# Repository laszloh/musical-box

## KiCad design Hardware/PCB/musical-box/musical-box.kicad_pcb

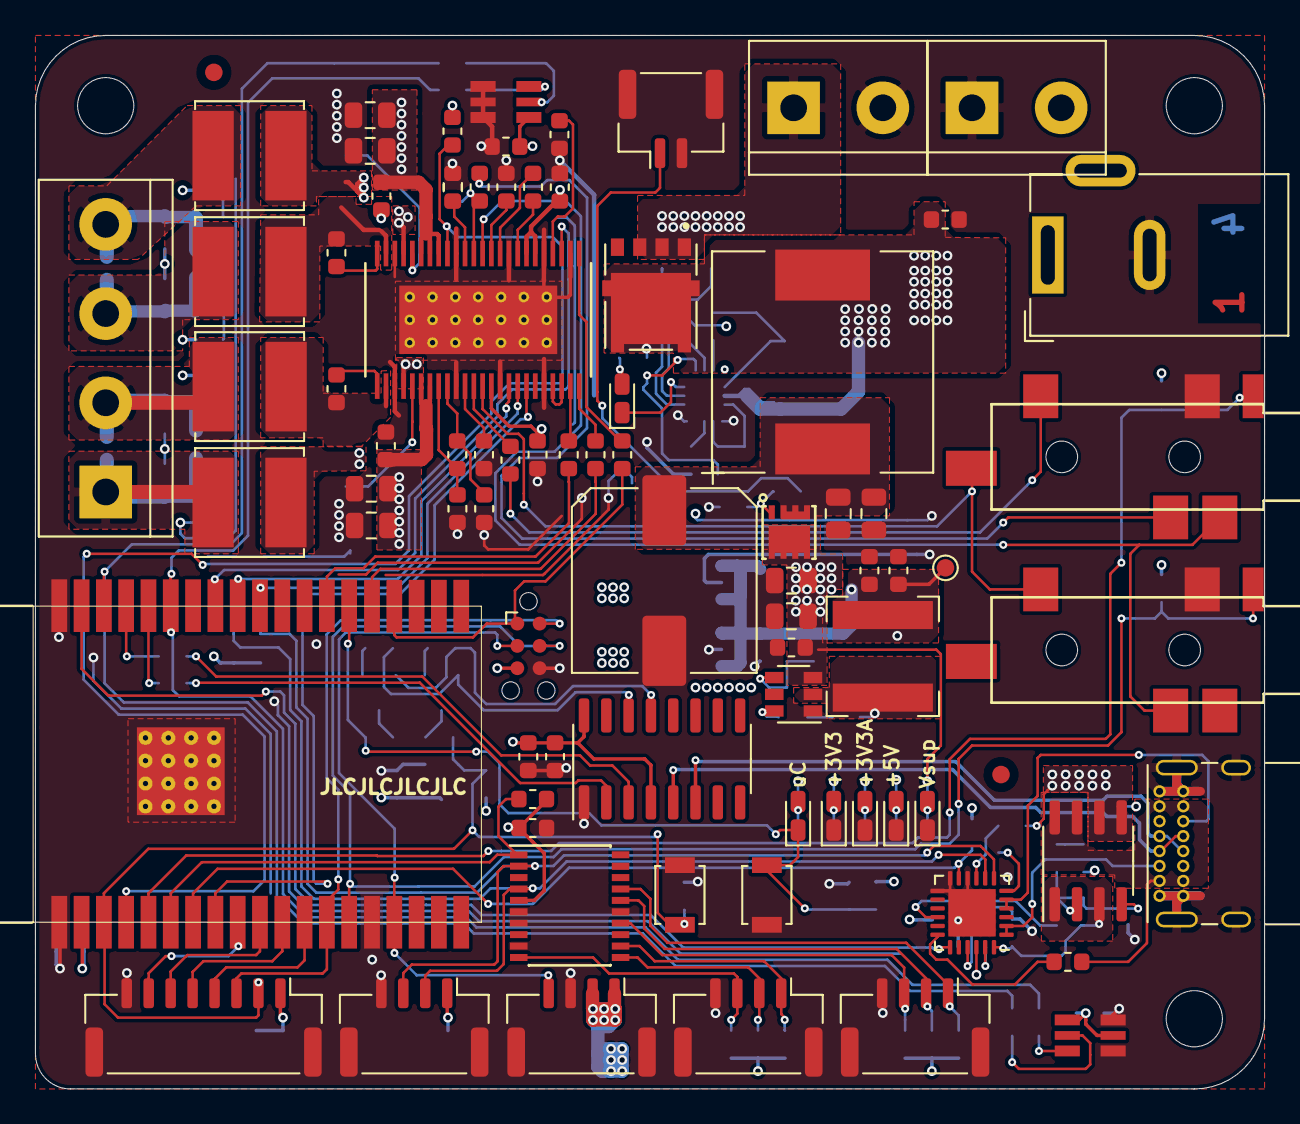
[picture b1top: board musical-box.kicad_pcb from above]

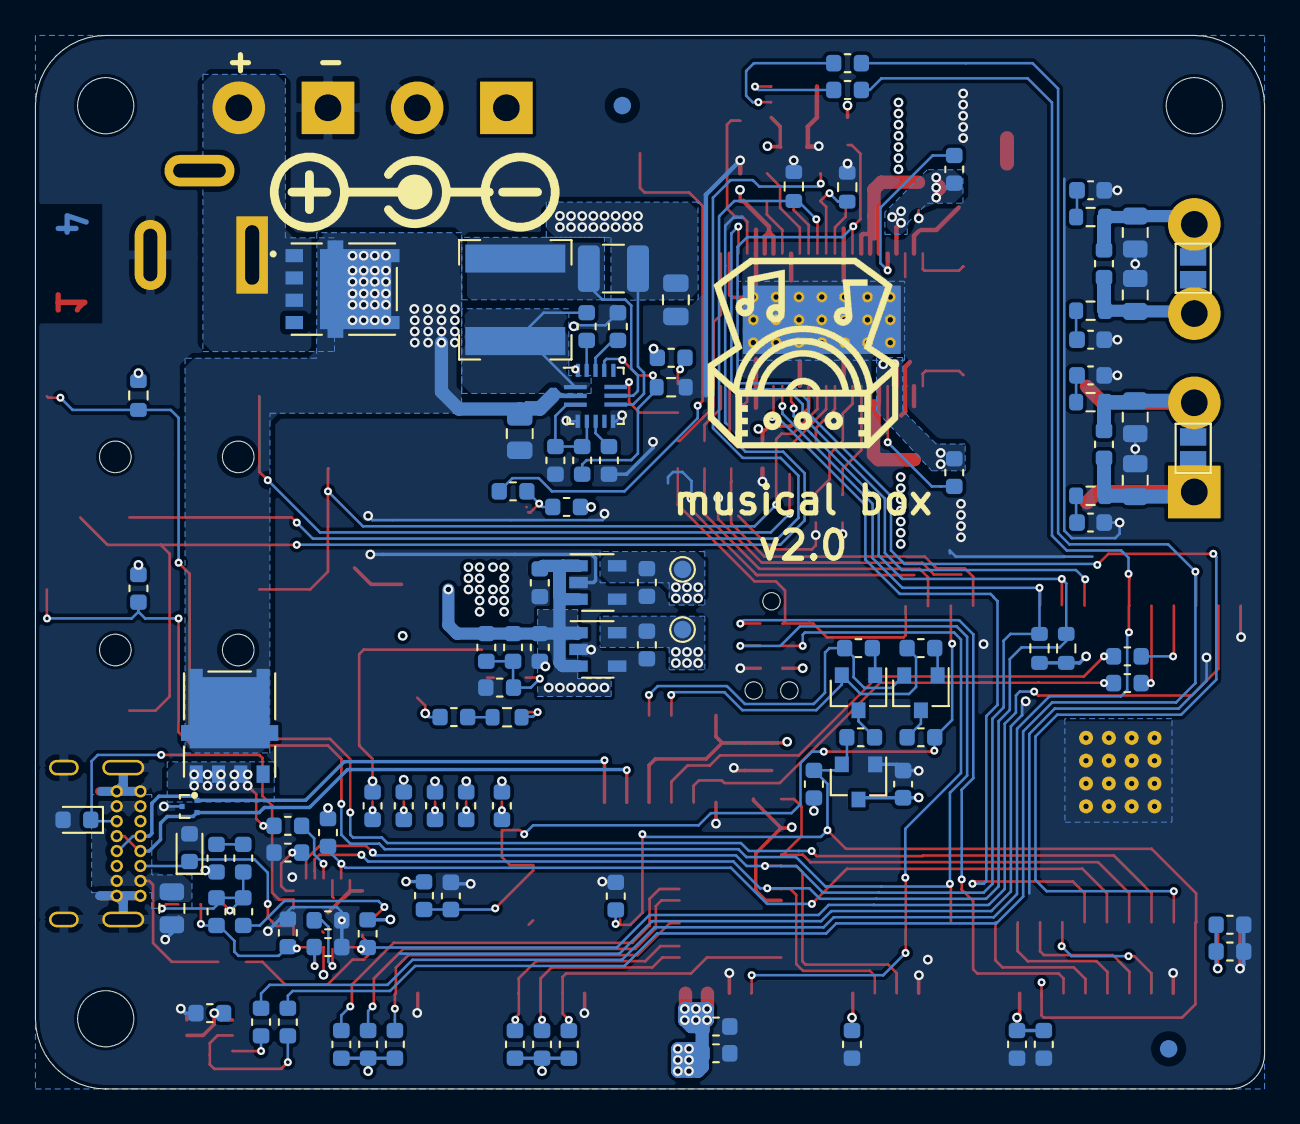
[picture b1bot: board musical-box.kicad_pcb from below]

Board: 4 copper layers, 70.0 x 60.0 mm, 192 parts (107 on the bottom side), 121 nets.

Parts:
C201, C203, C207, C211, C212, C218, C222, C505, C506, C527, C528: 10u; C_0805_2012Metric
C202: 270u; CP_Elec_10x10
C204, C208, C209, C214, C215, C301, C303, C402, C406, C503, C507, C511, C512, C517, C518, C521, C522, C524, C525: 2.2u; C_0603_1608Metric
C205, C206, C213, C216, C223, C224, C225, C227, C302, C304, C305, C306, C401, C403, C404, C405, C501, C502, C504, C508, C513, C515, C520, C526: 100n; C_0603_1608Metric
C217, C220, C221, C226: 22u; C_0603_1608Metric
C219, C510, C519: 100p; C_0603_1608Metric
C509, C514, C516, C523: 680n; C_0805_2012Metric
C529, C530, C531, C532: 10n; C_0603_1608Metric
D102, D203, D205, D207, D208, D209: LED; LED_0603_1608Metric_Castellated
D201, D204, D210: NTS1045EMFST1G; DIO_NTS1045EMFST1G
D202, D206: 24V; D_0603_1608Metric
FID101, FID102, FID103, FID104: Fiducial; Fiducial_1mm_Mask2mm
H101, H102, H104: MountingHole; MountingHole_3.2mm_M3
J1: power; JST_GH_BM02B-GHS-TBT_1x02-1MP_P1.25mm_Vertical
J201: PSU; TerminalBlock_bornier-2_P5.08mm
J202: Jack-DC; BarrelJack_Wuerth_6941xx301002
J203: BATT; TerminalBlock_bornier-2_P5.08mm
J301: JTAG; Tag-Connect_TC2030-IDC-NL_2x03_P1.27mm_Vertical
J401: SPI Display; JST_GH_BM08B-GHS-TBT_1x08-1MP_P1.25mm_Vertical
J402: Rotary Encoder 1; JST_GH_BM04B-GHS-TBT_1x04-1MP_P1.25mm_Vertical
J403: I2C Display; JST_GH_BM04B-GHS-TBT_1x04-1MP_P1.25mm_Vertical
J404: Rotary Encoder 2; JST_GH_BM04B-GHS-TBT_1x04-1MP_P1.25mm_Vertical
J405: WS2812; JST_GH_BM04B-GHS-TBT_1x04-1MP_P1.25mm_Vertical
J501: spk_out; TerminalBlock_bornier-4_P5.08mm
J502: aux in; PJ328B
J503: line out; PJ328B
JP3, JP4: mono; SolderJumper-2_P1.3mm_Open_Pad1.0x1.5mm
L201: 2,2u; L_12x12mm_H8mm
L202, L203: 6.8u; L_Bourns-SRN6028
L501, L502, L503, L504: 4.7u; L_Bourns_SRN6045TA
P201: USB_C; USB_C_Receptacle_GCT_USB4085
P202, P203, P204: ICT-Point; TestPoint_Pad_D1.0mm
Q201: IRFHM9331; PQFN-3x3
Q204: IRF9362; SOIC-8_3.9x4.9mm_P1.27mm
Q301, Q302: BC848; SOT-23
R101, R102, R103, R223, R501, R504, R505, R512: 10R; R_0603_1608Metric
R105, R106, R107, R207, R210, R217, R218, R221, R222, R305, R308, R312, R401, R402, R403, R404, R405, R406: 1k; R_0603_1608Metric
R201, R203, R205, R208, R209, R211, R213, R214, R215, R216, R220, R407, R409, R508, R509, R513: 10k; R_0603_1608Metric
R202, R204: 100k; R_0603_1608Metric
R206, R302, R303, R304, R309: 220R; R_0603_1608Metric
R212: 100mR; R_1210_3225Metric
R219: 52.3k; R_0603_1608Metric
R408, R410: 50m; R_0603_1608Metric
R502: 750k; R_0603_1608Metric
R503: 150k; R_0603_1608Metric
R506, R507, R510, R511: 3.3R; R_0603_1608Metric
SW301: boot; SW_SPST_B3U-1000P
SW302: reset; SW_SPST_B3U-1000P
U201: STUSB4500QTR; QFN-24-1EP_4x4mm_P0.5mm_EP2.7x2.7mm
U202: MP2615; QFN-16_2.9x2.9_Pitch0.5mm
U203: TPS56339; SOT-23-6
U204, U205: TLV75733PDBV; SOT-23-5
U206: TLV803EC30DBZR; SOT-23
U207: TPD2EUSB30A; Texas_DRT-3
U301: CH340C; SOIC-16_3.9x9.9mm_P1.27mm
U302: ESP32-WROVER
U401: PCF8574ATS; SSOP-20_4.4x6.5mm_P0.65mm
U501, U502: SPH0644HM4H-1
U503: TAS5754MDCA

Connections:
+3.3VA: C226.2, C501.1, C502.1, C507.1, P203.1, R221.2, U205.5, U501.1, U501.5, U502.1, U503.14
+3V3: C221.2, C227.2, C301.1, C302.1, C303.1, C304.1, C401.1, C402.1, C403.1, C404.1, C524.1, J301.5, J401.1, J403.1, P202.1, R105.2, R106.2, R107.2, R213.1, R214.1, R217.2, R222.1, R312.2, R401.1, R402.1, R403.1, R404.1, R405.1, R406.1, R407.1, R508.2, R509.2, R513.2, U201.22, U204.5, U206.3, U301.4, U301.16, U302.2, U401.5, U503.30, U503.31
+5V: C217.2, C219.2, C220.2, C223.2, C225.2, C405.1, C406.1, J405.1, J405.2, L203.2, P204.1, R218.2, R219.1, U204.1, U204.3, U205.1, U205.3
+15V: C218.2, C222.2, C224.2, C504.1, C505.1, C506.1, C526.1, C527.1, C528.1, Q201.3, R201.2, U203.3, U503.6, U503.7, U503.41, U503.42, U503.43
/Audio Output/AUX_Detect: J502.S, R513.1, U302.5
/Audio Output/DAC_OUTA: J502.TN, J503.T, U503.13
/Audio Output/DAC_OUTB: J502.R1N, J503.R1, R409.2, U503.36
/Audio Output/GPIO0: U302.8, U503.18
/Audio Output/GPIO2: U503.21, U503.22
/Audio Output/LRCLK: R101.1, U503.25
/Audio Output/OUT1+: C509.1, C510.1, J501.1, JP3.1, L501.2, R506.2
/Audio Output/OUT1-: C510.2, C514.1, J501.2, JP3.2, L502.2, R507.2
/Audio Output/OUT2+: C519.2, C523.1, J501.4, JP4.2, L504.2, R511.2
/Audio Output/OUT2-: C516.1, C519.1, J501.3, JP4.1, L503.2, R510.2
/Audio Output/SCLK: R102.1, U503.23
/Audio Output/SDIN: R103.1, U503.24
/Audio Output/SPKA_OUT+: C508.1, L501.1, U503.4
/Audio Output/SPKA_OUT-: C513.1, L502.1, U503.2
/Audio Output/SPKB_OUT+: C520.1, L504.1, U503.45
/Audio Output/SPKB_OUT-: C515.1, L503.1, U503.47
/Audio Output/SPK_INA: C511.1, J502.T
/Audio Output/SPK_INB: C525.2, J502.R1
/Audio Output/SPK_INB+: C525.1, R408.2, U503.37
/Audio Output/SPK_INB-: C522.2, R410.2, U503.38
/Microcontroller/D+: P201.A6, P201.B6, U207.1, U301.5
/Microcontroller/D-: P201.A7, P201.B7, U207.2, U301.6
/Microcontroller/DTR: Q302.2, R305.2, U301.13
/Microcontroller/I34: R407.2, U302.6, U401.1
/Microcontroller/I35: R214.2, U201.11, U302.7
/Microcontroller/I36: R508.1, U302.4, U503.40
/Microcontroller/IO00: C305.1, D102.1, R309.1, R312.1, SW301.2, U302.25
/Microcontroller/IO02: R103.2, U302.24
/Microcontroller/IO04: R102.2, U302.26
/Microcontroller/IO05: J403.3, R106.1, U201.7, U302.29, U401.2, U503.17
/Microcontroller/IO12: J301.4, J503.S, R509.1, U302.14
/Microcontroller/IO13: J301.3, J405.4, U302.16
/Microcontroller/IO14: J301.2, J401.3, U302.13
/Microcontroller/IO15: J301.1, R101.2, U302.23
/Microcontroller/IO18: J403.2, R107.1, U201.8, U302.30, U401.4, U503.16
/Microcontroller/IO19: U302.31, U503.27
/Microcontroller/IO21: R501.2, R505.2, U302.33
/Microcontroller/IO22: R504.2, R512.2, U302.36
/Microcontroller/IO23: R213.2, U201.19, U302.37
/Microcontroller/IO25: J401.6, U302.10
/Microcontroller/IO26: J401.5, U302.11
/Microcontroller/IO27: J401.4, U302.12
/Microcontroller/RTS: Q301.2, R308.2, U301.14
/Microcontroller/RXD0: R302.1, U302.34
/Microcontroller/TXD0: R303.1, U302.35
/Microcontroller/~RESET: C306.1, J401.2, R222.2, R304.2, SW302.2, U206.2, U302.3
/User Interface/BLED: J401.7, U302.9
GND: C201.1, C202.2, C203.1, C204.2, C206.1, C207.1, C208.2, C209.2, C211.1, C212.1, C214.1, C215.1, C217.1, C218.1, C220.1, C221.1, C222.1, C223.1, C224.1, C225.1, C226.1, C227.1, C301.2, C302.2, C303.2, C304.2, C305.2, C306.2, C401.2, C402.2, C403.2, C404.2, C405.2, C406.2, C501.2, C502.2, C503.2, C504.2, C505.2, C506.2, C507.2, C509.2, C512.1, C514.2, C516.2, C517.2, C521.2, C522.1, C523.2, C524.2, C526.2, C527.2, C528.2, C529.2, C530.2, C531.2, C532.2, D202.2, D203.1, D206.2, D207.1, D208.1, D209.1, J1.2, J1.MP, J201.1, J202.2, J203.2, J301.6, J401.8, J401.MP, J402.4, J402.MP, J403.4, J403.MP, J404.4, J404.MP, J405.3, J405.MP, J502.R2, J503.R2, P201.A1, P201.A12, P201.B1, P201.B12, P201.S1, R203.2, R209.2, R216.1, R220.1, R408.1, R409.1, R410.1, R502.1, SW301.1, SW302.1, U201.10, U201.12, U201.13, U201.25, U202.4, U202.8, U202.16, U203.1, U204.2, U204.4, U205.2, U205.4, U206.1, U207.3, U301.1, U302.1, U302.15, U302.38, U302.39, U401.6, U401.7, U401.9, U401.15, U501.4, U501.6, U502.4, U502.5, U502.6, U503.3, U503.10, U503.15, U503.20, U503.26, U503.29, U503.33, U503.39, U503.46, U503.EPAD
unnamed: C201.2, C202.1, C207.2, L201.2, Q201.2, R202.2
unnamed: C203.2, P201.A4, P201.A9, P201.B4, P201.B9, Q204.7, Q204.8, R207.1
unnamed: C204.1, Q204.1, Q204.3, R204.1, U201.24
unnamed: C205.1, R206.1
unnamed: C206.2, C211.2, D201.1, D204.1, D210.1, L201.1, R211.2, U202.2
unnamed: C208.1, U201.21
unnamed: C209.1, U201.23
unnamed: C212.2, D204.2, J203.1, R212.2, U202.9
unnamed: C213.1, U202.15
unnamed: C213.2, L202.1, U202.1
unnamed: C215.2, U202.14
unnamed: C216.1, R223.1
unnamed: C216.2, L203.1, U203.2
unnamed: C219.1, R219.2, R220.2, U203.4
unnamed: C503.1, R503.2, U503.8
unnamed: C508.2, U503.5
unnamed: C511.2, U503.12
unnamed: C512.2, U503.11
unnamed: C513.2, U503.1
unnamed: C515.2, U503.48
unnamed: C517.1, U503.28
unnamed: C518.1, U503.32
unnamed: C518.2, U503.34
unnamed: C520.2, U503.44
unnamed: C521.1, U503.35
unnamed: C529.1, R506.1
unnamed: C530.1, R507.1
unnamed: C531.1, R510.1
unnamed: C532.1, R511.1
unnamed: D102.2, R105.1
unnamed: D201.2, J201.2, J202.1
unnamed: D202.1, P201.B5, U201.4, U201.5
unnamed: D203.2, R201.1
unnamed: D205.1, U202.11
unnamed: D205.2, R211.1
unnamed: D206.1, P201.A5, U201.1, U201.2
unnamed: D207.2, R217.1
unnamed: D208.2, R218.1
unnamed: D209.2, R221.1
unnamed: J1.1, R205.1
unnamed: J402.1, R401.2, U401.12
unnamed: J402.2, R402.2, U401.11
unnamed: J402.3, R403.2, U401.10
unnamed: J404.1, R404.2, U401.17
unnamed: J404.2, R405.2, U401.16
unnamed: J404.3, R406.2, U401.14
unnamed: L202.2, R212.1, U202.10
unnamed: Q201.1, R202.1, R205.2
unnamed: Q204.2, Q204.4, R204.2, R206.2, R208.1
unnamed: Q301.1, R305.1
unnamed: Q301.3, R304.1
unnamed: Q302.1, R308.1
unnamed: Q302.3, R309.2
unnamed: R203.1, R215.2, U202.13
unnamed: R207.2, U201.18
unnamed: R208.2, U201.16
unnamed: R209.1, U201.6
unnamed: R210.2, U201.9
unnamed: R216.2, U202.6
unnamed: R223.2, U203.6
unnamed: R302.2, U301.2
unnamed: R303.2, U301.3
unnamed: R501.1, U501.3
unnamed: R502.2, R503.1, U503.9
unnamed: R504.1, U502.2
unnamed: R505.1, U502.3
unnamed: R512.1, U501.2
VCC: C214.2, R215.1, U202.3, U202.5
VDC: C205.2, D210.2, Q204.5, Q204.6, R210.1

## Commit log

2020-07-25 Add framework for project
    Add the framework for the project and add the needed submodules and ingores for the KiCad project.
2020-07-28 Add Software framework
    Add the Software framework. Custom PIO platform for ADF does not yet work. Need more work
2020-07-29 prepare software framework
2020-07-31 Start the schematic development
    Start work on the ESP and the audio output schematic
2020-07-31 Add MIC ADC
    Add the PCM1865 as the microphone ADC. It's still an open question, if
    it'll work.
    ToDo:
    check I2S data format, if it supports 4 channels in a 2x32bit frame
2020-08-03 Upload of the weekend work
2020-08-03 Further work on schematic done
    Pinout, outputs, UI is mostly finished. Power supply still missing.
    Free as many pins for JTAG as possible.
2020-08-04 Add 2 MEMS Mic's and change WS2812 driver to SPI
    Add 2 MEMS Microphones to the 2nd I2S channel and change the WS2812
    driver to use Monoflops and the SPI bus. Currently not the best
    solution.
    ToDo:
    -) Check memory footprint of the solution using the RMT module of the
    esp32 for the signal generation
2020-08-05 Small schematic update
2020-08-05 Update gitignore for LTSpice
    Update gitinore for LTSpice files and fix the monistable
    multivibrator values
2020-08-24 Work on the schematic and the layout
2020-08-26 Add ADF software framework
2020-08-28 Add board def files
2020-09-01 layout start
    layout start
2020-09-01 nightly commit -- squash me later
2020-09-02 Update schematic for new I2S amplifier
2020-09-02 Add 2S LiIon battery charger and assing missing footprints
2020-09-02 Rework USB-C power device schematic
    Rework the power device schematic to represent the typical application
    from the datasheet. Also remove all local footprint libraries.
2020-09-03 Fix short between SCL and SDA in netlist
2020-09-04 Start to add purchase numbers for the parts
    Start to select real parts from rs-components and digikey. Footprints were updated to reflect smaller package sizes found.
2020-09-08 Add two buttons for reset and bootloader
2020-12-15 Add new schematic and layout framework
2020-12-19 Change the audio jack to a cheaper one from ali
2020-12-23 Start working on placement and layout
2020-12-25 Finish v1 layout
    Cleanup still needed
2020-12-25 Add 3D models nd swap USB C connector to an avaliable one
2020-12-26 Start the work on the software framework
2020-12-26 Add ideal diodes with LTC4412 & IRF9362TRPBF instead of real diodes
2020-12-26 Further work on the layout
    Get back to diodes, since they are cheaper
2020-12-29 Reduce PCB by 15mm on one edge
    New PCB size is 70x60mm through better positioning and higher packing
    ratio.
2020-12-30 No unconnected nets any more
2020-12-30 Layout optimizations
2021-01-03 Layout optimisations
2021-01-06 layoutoptimisation and review
2021-01-06 Start layout rework
    Added AUX-in connector and changed line in to have only a single
    connector type. Due to the change, the power part has to be reworked.
    First part placement is finished, layout work still ongoing.
2021-01-07 Change Capatictor size to 0805
    Reduce the package size of the input filter capacitors
2021-01-07 Connect Line and AUX in detect to VDD3D
2021-01-07 Route power LEDs
2021-01-07 Route the USB-Serial converter and port expander
2021-01-07 Route the VDD3A lines
2021-01-07 Route audio signals
2021-01-07 Fix battery charger circuit
2021-01-07 Swap aux and line detect for better routing
2021-01-07 Route aux and line detect
2021-01-07 Route Reset and IO0 stubs
2021-01-07 Fix Poly fills and add silk screen information
2021-01-07 Swap Q201 to DMP3013SFK since the old one has a EOL PCN
2021-01-07 Add 3D models for the remaining parts
2021-01-07 Add partnumber and supplier for audio jack
2021-01-07 Add 3D models and update library
2021-01-07 Increase track width in inner layers to match needed current capabilities
2021-01-07 Add logo and version text to PCB
2021-01-09 review of layout optimizing routing
2021-01-09 shielding between i2s lines
2021-01-09 optimasation
2021-01-09 Fix: Change 3D path of audio jacks to relative
2021-01-09 Fix: Set Pin EN of U203 to DNC
    TPS56339 EN Pin set to DNC
2021-01-09 Fix: VFB Resistor change to 30.9k
    VFB Resistor R219 changed to 30.9k
2021-01-09 Fix: VBST series resistor added
    TPS56339 VBST series resisor R223 added
2021-01-10 Fix: VBUS EN resistor changed
    STUSB4500QTR VBUS_EN_SNK R206 changed to 100R
2021-01-10 Create Digikey_parts.xlsx
    Digikey Partlist
2021-01-12 Update Digikey_parts.xlsx
    Update Digikey Parts
2021-01-13 Swap J203 to a screwing block
2021-01-13 Swap Q201 to IRFHM9331
2021-01-14 Update footprints with the correct heat slugs and stencils
2021-01-14 Add 3D model of PCB
2021-01-15 Routing optimization to increase bottom GND pour around Audio AMP
2021-01-15 Add shielding to high frequency nets
2021-01-15 Add plain side for Speaker
    Add a plain side with holes for M3 ISO 4762 screws for the speaker body https://www.thingiverse.com/thing:4692880
2021-01-15 Round the PCB corners
    (cherry picked from commit 10227c025a6ee98868355f93265f09cbc06648e2)
2021-01-15 Add layer markers to pcb
2021-01-15 Remove unused git attribute and filter functions
2021-01-15 Create gerber and drill files for pcb production
2021-01-15 prepare zip file for jlcpcb prototype production
2021-01-16 Add resistors to enable PBTL mode of the TAS5754M
2021-01-16 Add barrel jack polarity symbol
2021-01-16 Fix: Add correct files to enable PBTL
2021-01-16 Create production files for v1.0-alpha release
2021-01-16 Add resistors to enable PBTL mode of the TAS5754M
    (cherry picked from commit 301159c7868d971a4884b90c71ce5df5829b466a)
2021-01-16 Add barrel jack polarity symbol
    (cherry picked from commit 159b1489efe9453d27f0acdcd18ccf6335c51b1f)
2021-01-16 Fix: Add correct files to enable PBTL
    (cherry picked from commit 20c2b4c278d97c62a54a61cca38bbc54ec631a1d)
2021-01-16 Update Sides to fit the housing and add a cover with coutouts for the PCB
2021-01-25 Modify copper pour to reduce marrow corssings
    At the liIon there are some narrow parts in the copper pour. This commit
    increases the pour
2021-02-10 RS components added
2021-02-18 Fix error in schematic
    The P-Channel MOSFet was connected in the wrong way, preventing the shutoff circuit from working properly
2021-02-18 CHange values to fit the TPS56339
2021-02-19 Bugfix: Add connection to VDD to supply the PD device
2021-02-20 Adapt values to real population
2021-02-20 Add test SW for the STUSB4500
2021-02-20 Addendum to 9e53ee1
2021-02-20 Remove needless vias
2021-02-20 Add I2C scanner test tool
2021-02-20 Add TAS5754M test code
2021-02-21 Reduce part diversity
2021-02-21 Add working TAS5754 testing
2021-02-21 Bugfix: Fix speaker B connection to make the output work
2021-02-21 Reduce part count on the USB PD device and add some ESD protection
2021-02-21 Reduce number of unique parts
2021-02-22 Add squeezelite submodule
2021-02-23 Remove USB from PCB in favor of a programming interface
2021-02-23 Reposition the ESP
2021-02-23 Change 22uF capacitors to 2.2uF to reduce costs
2021-02-23 Add JTAG connector and move to SOT-23 single transistors
2021-02-28 Bugfix: Missing NTC voltage divider added
2021-03-03 fix error in mono setup
2021-04-10 Add production files for v2.0
2021-06-23 Add programming files for STUSB4500
2021-06-25 Add additional diode to isolate USB-C from the main power supply

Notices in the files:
parts and their libraries:
Copyright 2016 Accelerated Designs. All rights reserved.
